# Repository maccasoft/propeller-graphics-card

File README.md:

## Propeller Graphics Card

Add-on board and firmware designed for the [RC2014](http://rc2014.co.uk/) computer to provide graphics capabilities.

### Specifications

 * Resolution up to 320x240 pixels with 64 colors
 * Tile graphics with 8x8 pixels tiles
 * Sprites with 8x8 up to 32x32 pixels
 * Full screen scroll
 * Overlays for score and indicators
 * Bitmap graphics modes 320x240x3bpp, 256x192x4bpp and 256x224x4bpp
 * RGB PAL, NTSC and VGA output

The board uses I/O ports **40H, 41H, 42H and 43H** for programming.

See the [Wiki](https://github.com/maccasoft/propeller-graphics-card/wiki) pages for the documentation.

### Schematic

| Parts List            |                     |          |                                 |
| --------------------- | ------------------- | -------- | ------------------------------- |
| R1, R2, R16-R31       | 4.700 ohm 1/4 watt  | IC1      | MCP1700-3302E/TO                |
| R3                    | 1.200 ohm 1/4 watt  | IC2      | P8X32A-D40                      |
| R4                    | 33.000 ohm 1/4 watt | IC3      | 24LC512                         |
| R5, R7, R9            | 510 ohm 1/4 watt 1% | TR1      | NPN Transistor BC547            |
| R6, R8, R10, R11, R12 | 240 ohm 1/4 watt 1% | JP1      | 3 pin male header               |
| R13, R14, R15         | 130 ohm 1/4 watt 1% | JP2      | 1 pin male header               |
| R32, R33, R34         | 10.000 ohm 1/4 watt | JP3, JP4 | 2 pin male header               |
| C1, C5                | 10 uF 63v elettr.   | CN1      | 40 pin male header, right angle |
| C2, C3, C4            | 100.000 pF poly.    | CN2      | DB15 HD female connector        |
| D1, D2, D3, D4, D5    | 1N4148              | CN4      | 5 pin male header               |
| XTAL1                 | 5 MHz crystal       |          |                                 |

Board shared on [OSHPark](https://oshpark.com/shared_projects/1gud4wQD) and available on [Tindie](https://www.tindie.com/stores/maccasoft/).

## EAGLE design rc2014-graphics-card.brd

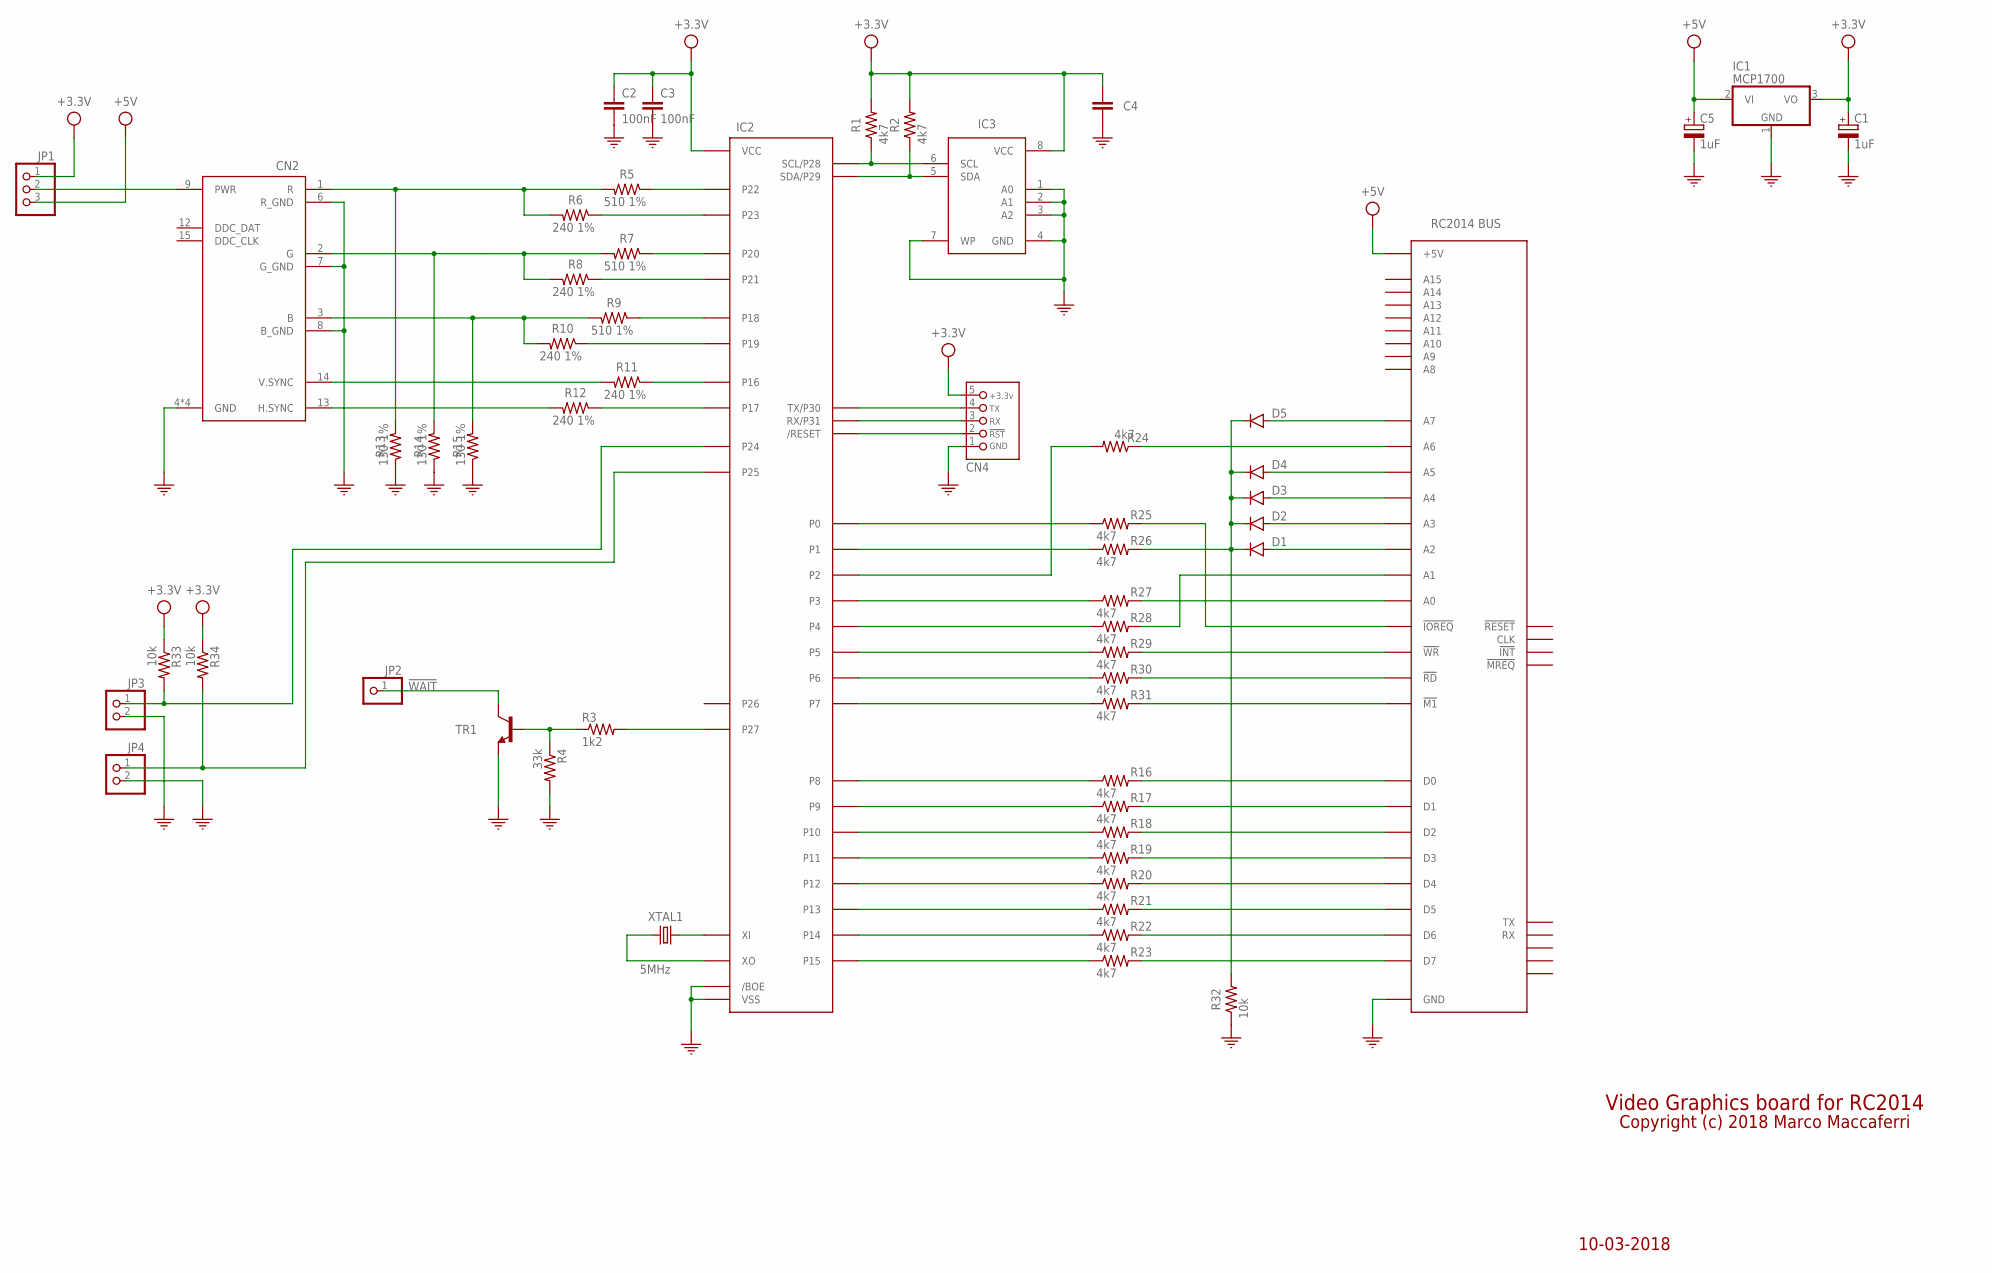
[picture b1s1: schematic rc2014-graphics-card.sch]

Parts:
C1, C5: 1uF; E2,5-6; MPN ESK105M050AC3AA
C2, C3, C4: 100nF; C050-025X075; MPN R82EC3100AA70J
CN1: RC2014BUS; MPN PRPC040SBAN-M71RC
CN2: VGA; MPN 1734344-1
CN4: PROPELLER_ICSP_HEADER; HEADER_PRG_1X05; MPN PRPC005SAAN-RC
D1, D2, D3, D4, D5: 1N4148DO35-7; DO35-7
IC1: MCP1700; TO92; MPN MCP1700-3302E/TO
IC2: P8X32A-B-D40; DIL40; MPN P8X32A-D40
IC3: 24LC512-I/P; DIL08; MPN 24LC256-I/P
JP1: PINHD-1X3; 1X03
JP2: PINHD-1X1; 1X01
JP3, JP4: PINHD-1X2; 1X02
R1, R2: 4k7; 0207/10; MPN CFR-25JB-52-4K7
R3: 1k2; 0207/10
R4: 33k; 0204/7
R5, R7, R9: 510 1%; 0207/10; MPN RNMF14FTC510R
R6, R8, R10, R11, R12: 240 1%; 0207/10; MPN RNMF14FTC240R
R13, R14, R15: 130 1%; 0207/10; MPN RNMF14FTC130R
R16, R17, R18, R19, R20, R21, R22, R23, R24, R25, R26, R27, R28, R29, R30, R31: 4k7; 0204/7
R32: 10k; 0204/7
R33, R34: 10k; 0207/10
TR1: BC547A; TO92
XTAL1: 5MHz; HC49/S; MPN ECS-50-20-4X

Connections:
!IOREQ!: IC2.1 (P0), R25.1
!M1!: IC2.8 (P7), R31.1
!RD!: IC2.7 (P6), R30.1
!WAIT!: JP2.1, TR1.1 (C)
!WR!: IC2.6 (P5), R29.1
+3.3V: C1.+, C2.1, C3.1, C4.1, CN4.5, IC1.3 (VO), IC2.12 (VCC), IC2.32 (VCC), IC3.8 (VCC), JP1.1, R1.2, R2.2, R33.1, R34.1
+5V: C5.+, CN1.+5V, IC1.2 (VI), JP1.3
A0: IC2.4 (P3), R27.1
A1: IC2.5 (P4), R28.1
A6: IC2.3 (P2), R24.2
ADDR: IC2.2 (P1), R26.1
B: CN2.3 (B), R9.2, R10.2, R15.2
D0: IC2.13 (P8), R16.1
D1: IC2.14 (P9), R17.1
D2: IC2.15 (P10), R18.1
D3: IC2.16 (P11), R19.1
D4: IC2.17 (P12), R20.1
D5: IC2.18 (P13), R21.1
D6: IC2.19 (P14), R22.1
D7: IC2.20 (P15), R23.1
G: CN2.2 (G), R7.2, R8.2, R14.2
GND: C1.-, C2.2, C3.2, C4.2, C5.-, CN1.GND, CN2.4 (GND), CN2.5 (GND), CN2.6 (R_GND), CN2.7 (G_GND), CN2.8 (B_GND), CN2.10 (GND), CN2.11 (GND), CN4.1, IC1.1 (GND), IC2.9 (VSS), IC2.10 (/BOE), IC2.29 (VSS), IC3.1 (A0), IC3.2 (A1), IC3.3 (A2), IC3.4 (GND), IC3.7 (WP), JP3.2, JP4.2, R4.2, R13.1, R14.1, R15.1, R32.1, TR1.3 (E)
GPU_SCL: IC2.37 (SCL/P28), IC3.6 (SCL), R1.1
GPU_SDA: IC2.38 (SDA/P29), IC3.5 (SDA), R2.1
HSYNC: CN2.13 (H.SYNC), R12.2
unnamed: IC2.30 (XI), XTAL1.1
unnamed: IC2.31 (XO), XTAL1.2
unnamed: CN1.D3, R19.2
unnamed: CN1.D2, R18.2
unnamed: CN1.D1, R17.2
unnamed: CN1.D0, R16.2
unnamed: CN1.D4, R20.2
unnamed: CN1.D5, R21.2
unnamed: CN1.D6, R22.2
unnamed: CN1.D7, R23.2
unnamed: CN4.2, IC2.11 (/RESET)
unnamed: CN4.3, IC2.40 (RX/P31)
unnamed: CN4.4, IC2.39 (TX/P30)
unnamed: CN1.A3, D2.A
unnamed: CN1.A4, D3.A
unnamed: CN1.A5, D4.A
unnamed: CN1.A6, R24.1
unnamed: CN1.A7, D5.A
unnamed: D1.C, D2.C, D3.C, D4.C, D5.C, R26.2, R32.2
unnamed: CN1.A2, D1.A
unnamed: CN1.A1, R28.2
unnamed: CN1.A0, R27.2
unnamed: CN1.!RD!, R30.2
unnamed: CN1.!WR!, R29.2
unnamed: CN1.!M1!, R31.2
unnamed: CN1.!IOREQ!, R25.2
unnamed: CN2.9 (PWR), JP1.2
unnamed: R3.1, R4.1, TR1.2 (B)
unnamed: IC2.36 (P27), R3.2
unnamed: IC2.33 (P24), JP3.1, R33.2
unnamed: IC2.34 (P25), JP4.1, R34.2
P16: IC2.21 (P16), R11.1
P17: IC2.22 (P17), R12.1
P18: IC2.23 (P18), R9.1
P19: IC2.24 (P19), R10.1
P20: IC2.25 (P20), R7.1
P21: IC2.26 (P21), R8.1
P22: IC2.27 (P22), R5.1
P23: IC2.28 (P23), R6.1
R: CN2.1 (R), R5.2, R6.2, R13.2
VSYNC: CN2.14 (V.SYNC), R11.2

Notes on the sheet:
RC2014 BUS
Video Graphics board for RC2014
10-03-2018
Copyright (c) 2018 Marco Maccaferri

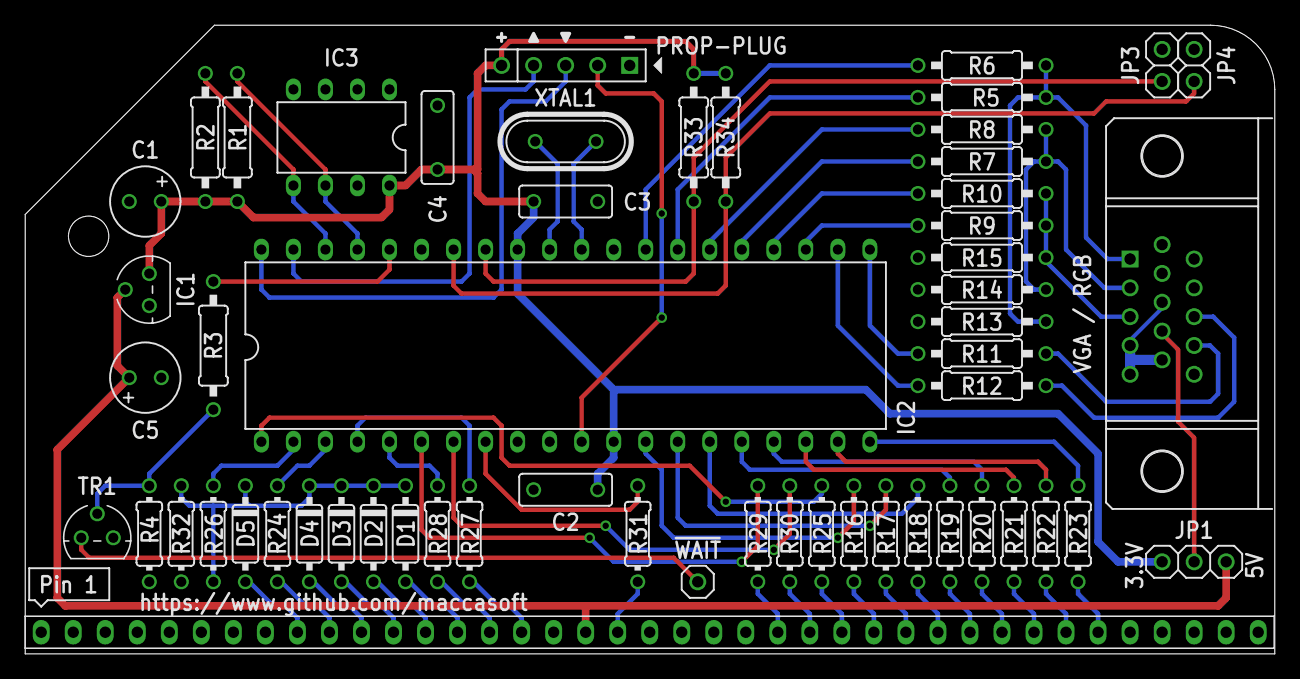
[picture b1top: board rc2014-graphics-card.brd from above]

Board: 2 copper layers, 99.1 x 49.9 mm, 56 parts (0 on the bottom side), 66 nets.

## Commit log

2018-03-10 Repository setup
2018-03-10 Added board image, schematics, gerbers and parts list
2018-03-13 Initial code commit
2018-03-13 Added schematic
2018-03-15 Implemented write pointer wrap
2018-03-26 Optimized offsets calculation
2018-04-06 Implemented firmware upload
2018-04-06 Added binary image export
2018-04-07 Implemented additional resolutions
2018-04-08 Fixed i2c bus release
2018-04-10 Added dependencies build for assembler files
2018-04-10 Implemented video mode loaders
2018-04-10 Sprites rendering optimizations
2018-04-10 Ignore eclipse project files
2018-04-10 Full screen scrolling
2018-04-11 Overlays
2018-04-12 Added software folder
2018-04-12 Fixed i2c eeprom writes
2018-04-15 Updated descriptions and links
2018-04-19 Use hub locations to pass parameters to video mode loaders
2018-04-19 Plain bitmap modes initial implementation
2018-04-20 Fixed source formatting inconsistencies
2018-04-20 Firmware upload code moved to include file
2018-04-20 Fixed palette write wrap
2018-04-21 Simplified firmware upload protocol
2018-04-21 Unified bitmap bus interface code
2018-04-21 Added raw bitmap video ram write command
2018-04-22 Changed 3bpp pixels packing
2018-04-22 Updated description
2018-04-22 Added color bars example
2018-04-24 Code cleanup
2018-04-28 Added graphics examples
2018-04-28 Removed binary files
2018-04-28 Updated descriptions
2018-12-04 Added TMS9918 emulation
2018-12-04 Added TMS9918 software examples
2018-12-31 Reset frame flag only when needed
2018-12-31 Added plasma example
2018-12-31 Code optimizations
2019-01-03 Optimized plasma effect
2019-01-31 Definitions cleanup
2019-01-31 Minimize bus trigger glitches
2019-01-31 Skip sprites with transparent color
